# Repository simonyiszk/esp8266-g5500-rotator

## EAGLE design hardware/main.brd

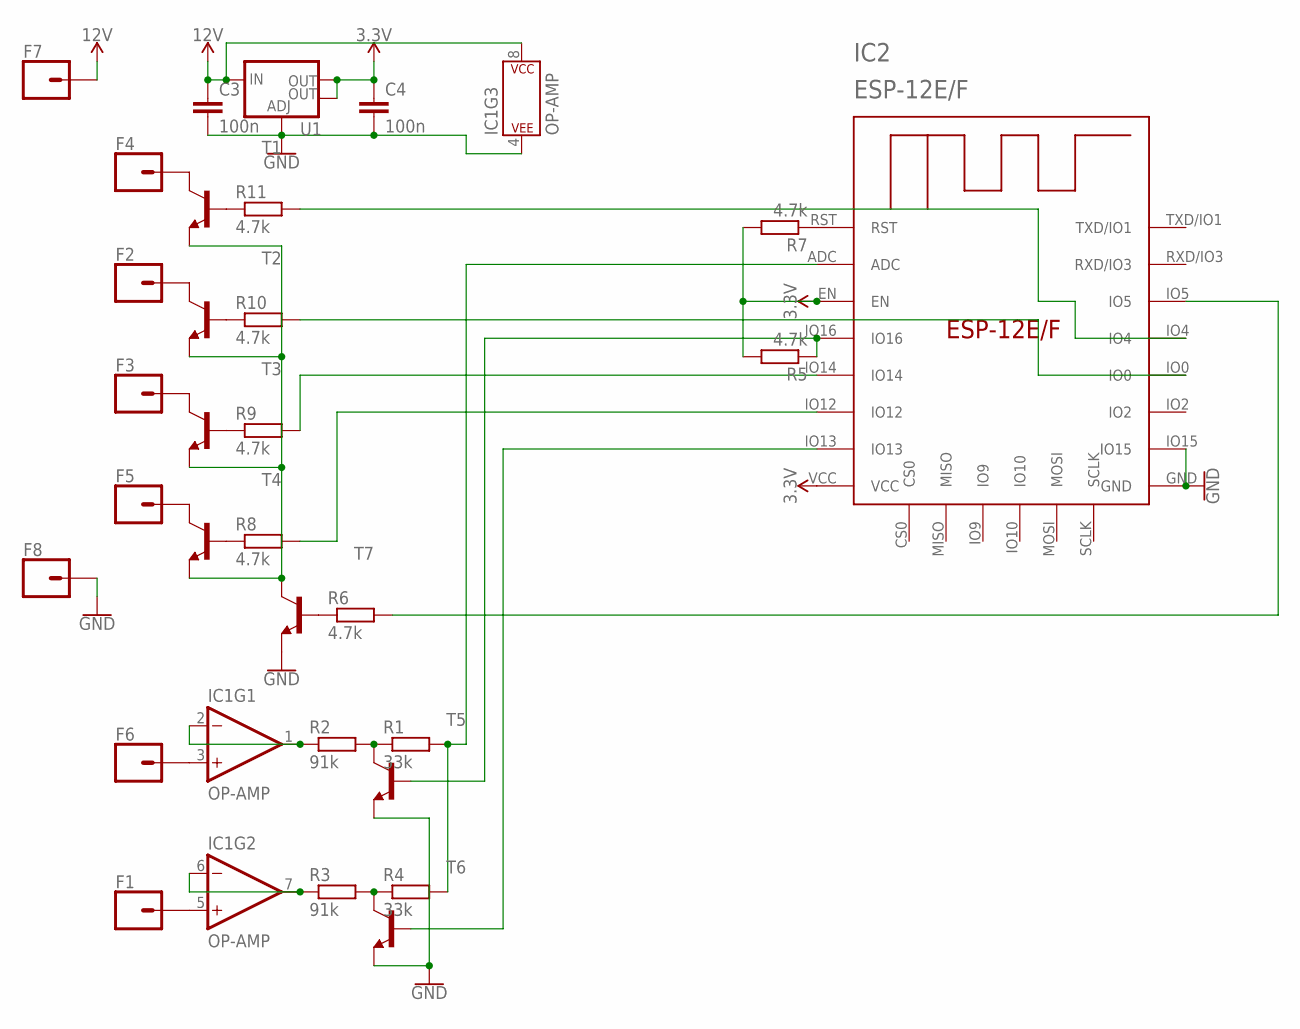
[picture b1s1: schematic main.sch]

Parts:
C3, C4: 100n; C0805K
F1, F2, F3, F4, F5, F6, F7, F8: CONN_01OFFSET; 1X01_OFFSET
IC1: OP-AMP; SO08
IC2: ESP-12E/F; ESP-12E
R1, R4: 33k; R0805
R2, R3: 91k; R0805
R5, R6, R7, R8, R9, R10, R11: 4.7k; R0805
T1, T2, T3, T4, T5, T6, T7: MMBT5551LT1-NPN-SOT23-BEC; SOT23-BEC
U1: V_REG_LM1117SOT223; SOT223

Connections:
3.3V: C4.1, IC2.EN, IC2.VCC, R5.2, R7.2, U1.2 (OUT), U1.4 (OUT)
12V: C3.1, F7.1, IC1.8 (P$V+), U1.3 (IN)
GND: C3.2, C4.2, F8.1, IC1.4 (P$V-), IC2.GND, IC2.IO15, T5.E, T6.E, T7.E, U1.1 (ADJ)
unnamed: F1.1, IC1.5 (+IN)
unnamed: F4.1, T1.C
unnamed: F2.1, T2.C
unnamed: F5.1, T4.C
unnamed: F3.1, T3.C
unnamed: F6.1, IC1.3 (+IN)
unnamed: T1.E, T2.E, T3.E, T4.E, T7.C
unnamed: R6.1, T7.B
unnamed: IC2.IO0, R10.2
unnamed: R1.1, R2.2, T5.C
unnamed: IC1.1 (OUT), IC1.2 (-IN), R2.1
unnamed: R3.2, R4.1, T6.C
unnamed: IC1.6 (-IN), IC1.7 (OUT), R3.1
unnamed: IC2.ADC, R1.2, R4.2
unnamed: IC2.IO4, R11.2
unnamed: IC2.IO5, R6.2
unnamed: R8.1, T4.B
unnamed: IC2.IO12, R8.2
unnamed: IC2.IO13, T6.B
unnamed: IC2.IO16, R5.1, T5.B
unnamed: IC2.RST, R7.1
unnamed: R9.1, T3.B
unnamed: R10.1, T2.B
unnamed: R11.1, T1.B
unnamed: IC2.IO14, R9.2

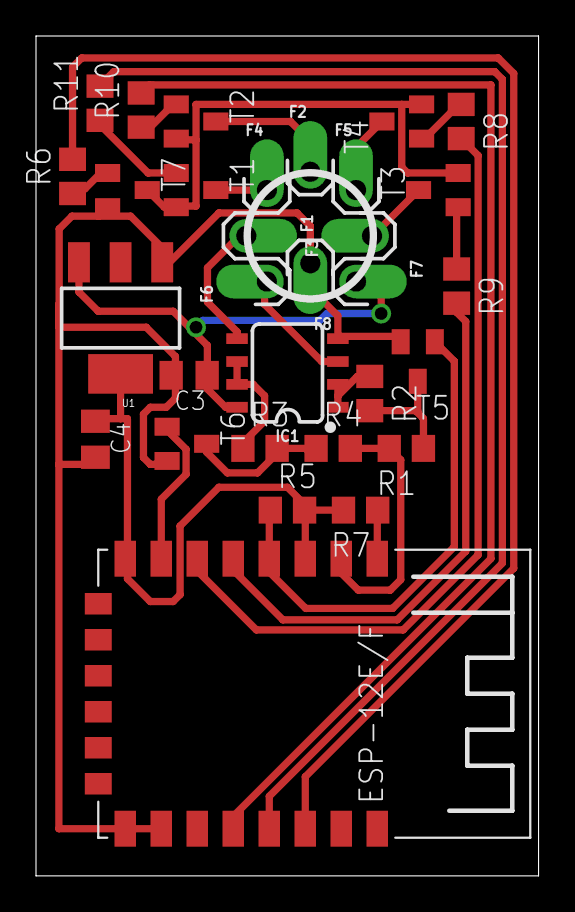
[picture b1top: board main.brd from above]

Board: 2 copper layers, 27.9 x 46.7 mm, 31 parts (0 on the bottom side), 28 nets.

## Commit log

2021-03-21 v2.1
2021-03-22 v2.2

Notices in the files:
parts and their libraries:
SparkFun-Connectors: Licensing: Creative Commons ShareAlike 4.0 International - https://creativecommons.org/licenses/by-sa/4.0
